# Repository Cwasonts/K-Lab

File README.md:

# K-Lab
storing boards I make for lab

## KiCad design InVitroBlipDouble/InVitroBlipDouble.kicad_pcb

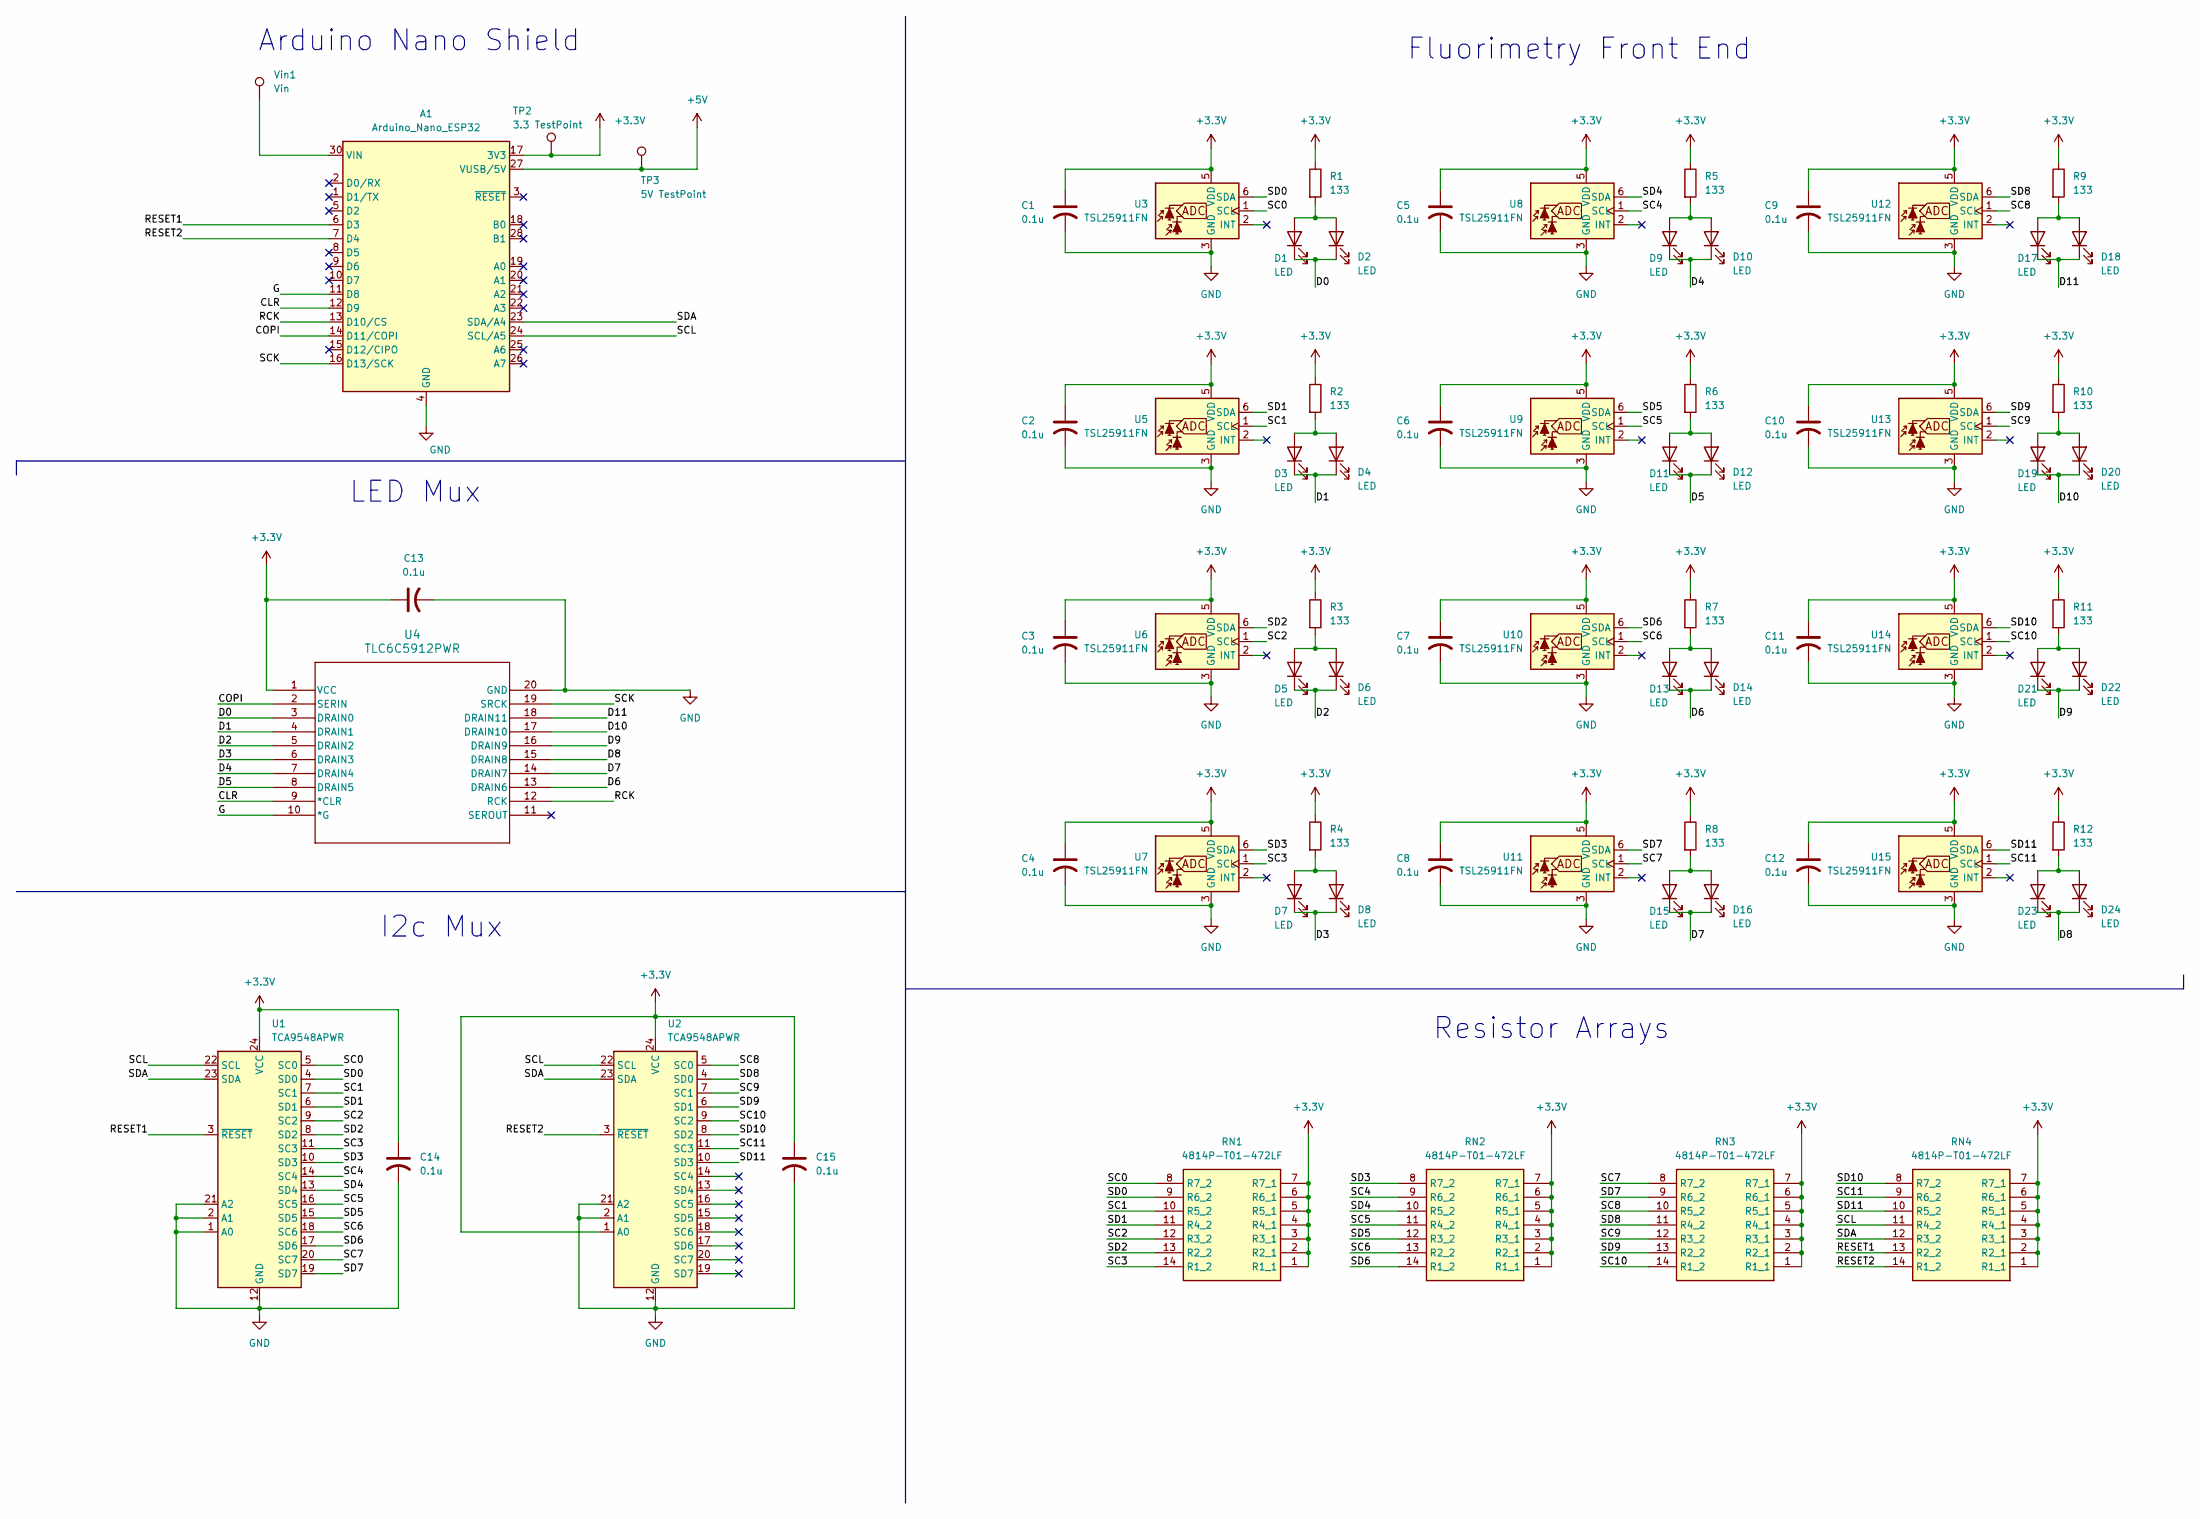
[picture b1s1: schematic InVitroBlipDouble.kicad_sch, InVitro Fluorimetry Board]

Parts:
A1: Arduino_Nano_ESP32; Arduino_Nano
C1, C2, C3, C4, C5, C6, C7, C8, C9, C10, C11, C12, C13, C14, C15: 0.1u; C_0603_1608Metric
D1, D2, D3, D4, D5, D6, D7, D8, D9, D10, D11, D12, D13, D14, D15, D16, D17, D18, D19, D20, D21, D22, D23, D24: LED; LED_Cree-XQ
R1, R2, R3, R4, R5, R6, R7, R8, R9, R10, R11, R12: 133; R_0603_1608Metric
RN1, RN2, RN3, RN4: 4814P-T01-472LF; 4814PT01472LF; Mouser Part Number 652-4814P-T1LF-4.7K
TP2: 3.3 TestPoint; TestPoint_Pad_2.5x2.5mm
TP3: 5V TestPoint; TestPoint_Pad_2.5x2.5mm
U1, U2: TCA9548APWR; TSSOP-24_4.4x7.8mm_P0.65mm
U3, U5, U6, U7, U8, U9, U10, U11, U12, U13, U14, U15: TSL25911FN; AMS_TSL25911FN
U4: TLC6C5912PWR; PW20_TEX
Vin1: Vin; TestPoint_Pad_2.5x2.5mm

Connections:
+3.3V: A1.17 (3V3), C1.1, C2.1, C3.1, C4.1, C5.1, C6.1, C7.1, C8.1, C9.1, C10.1, C11.1, C12.1, C13.1, C14.1, C15.1, R1.1, R2.1, R3.1, R4.1, R5.1, R6.1, R7.1, R8.1, R9.1, R10.1, R11.1, R12.1, RN1.1 (R1_1), RN1.2 (R2_1), RN1.3 (R3_1), RN1.4 (R4_1), RN1.5 (R5_1), RN1.6 (R6_1), RN1.7 (R7_1), RN2.1 (R1_1), RN2.2 (R2_1), RN2.3 (R3_1), RN2.4 (R4_1), RN2.5 (R5_1), RN2.6 (R6_1), RN2.7 (R7_1), RN3.1 (R1_1), RN3.2 (R2_1), RN3.3 (R3_1), RN3.4 (R4_1), RN3.5 (R5_1), RN3.6 (R6_1), RN3.7 (R7_1), RN4.1 (R1_1), RN4.2 (R2_1), RN4.3 (R3_1), RN4.4 (R4_1), RN4.5 (R5_1), RN4.6 (R6_1), RN4.7 (R7_1), TP2.1, U1.24 (VCC), U2.1 (A0), U2.24 (VCC), U3.5 (VDD), U4.1 (VCC), U5.5 (VDD), U6.5 (VDD), U7.5 (VDD), U8.5 (VDD), U9.5 (VDD), U10.5 (VDD), U11.5 (VDD), U12.5 (VDD), U13.5 (VDD), U14.5 (VDD), U15.5 (VDD); also elsewhere on the board
+5V: A1.27 (VUSB/5V), TP3.1; also elsewhere on the board
/CLR: A1.12 (D9), U4.9 (*CLR)
/COPI: A1.14 (D11/COPI), U4.2 (SERIN)
/D0: D1.1 (K), D2.1 (K), U4.3 (DRAIN0)
/D1: D3.1 (K), D4.1 (K), U4.4 (DRAIN1)
/D2: D5.1 (K), D6.1 (K), U4.5 (DRAIN2)
/D3: D7.1 (K), D8.1 (K), U4.6 (DRAIN3)
/D4: D9.1 (K), D10.1 (K), U4.7 (DRAIN4)
/D5: D11.1 (K), D12.1 (K), U4.8 (DRAIN5)
/D6: D13.1 (K), D14.1 (K), U4.13 (DRAIN6)
/D7: D15.1 (K), D16.1 (K), U4.14 (DRAIN7)
/D8: D23.1 (K), D24.1 (K), U4.15 (DRAIN8)
/D9: D21.1 (K), D22.1 (K), U4.16 (DRAIN9)
/D10: D19.1 (K), D20.1 (K), U4.17 (DRAIN10)
/D11: D17.1 (K), D18.1 (K), U4.18 (DRAIN11)
/G: A1.11 (D8), U4.10 (*G)
/RCK: A1.13 (D10/CS), U4.12 (RCK)
/RESET1: A1.6 (D3), RN4.13 (R2_2), U1.3 (~RESET)
/RESET2: A1.7 (D4), RN4.14 (R1_2), U2.3 (~RESET)
/SC0: RN1.8 (R7_2), U1.5 (SC0), U3.1 (SCL)
/SC1: RN1.10 (R5_2), U1.7 (SC1), U5.1 (SCL)
/SC2: RN1.12 (R3_2), U1.9 (SC2), U6.1 (SCL)
/SC3: RN1.14 (R1_2), U1.11 (SC3), U7.1 (SCL)
/SC4: RN2.9 (R6_2), U1.14 (SC4), U8.1 (SCL)
/SC5: RN2.11 (R4_2), U1.16 (SC5), U9.1 (SCL)
/SC6: RN2.13 (R2_2), U1.18 (SC6), U10.1 (SCL)
/SC7: RN3.8 (R7_2), U1.20 (SC7), U11.1 (SCL)
/SC8: RN3.10 (R5_2), U2.5 (SC0), U12.1 (SCL)
/SC9: RN3.12 (R3_2), U2.7 (SC1), U13.1 (SCL)
/SC10: RN3.14 (R1_2), U2.9 (SC2), U14.1 (SCL)
/SC11: RN4.9 (R6_2), U2.11 (SC3), U15.1 (SCL)
/SCK: A1.16 (D13/SCK), U4.19 (SRCK)
/SCL: A1.24 (SCL/A5), RN4.11 (R4_2), U1.22 (SCL), U2.22 (SCL)
/SD0: RN1.9 (R6_2), U1.4 (SD0), U3.6 (SDA)
/SD1: RN1.11 (R4_2), U1.6 (SD1), U5.6 (SDA)
/SD2: RN1.13 (R2_2), U1.8 (SD2), U6.6 (SDA)
/SD3: RN2.8 (R7_2), U1.10 (SD3), U7.6 (SDA)
/SD4: RN2.10 (R5_2), U1.13 (SD4), U8.6 (SDA)
/SD5: RN2.12 (R3_2), U1.15 (SD5), U9.6 (SDA)
/SD6: RN2.14 (R1_2), U1.17 (SD6), U10.6 (SDA)
/SD7: RN3.9 (R6_2), U1.19 (SD7), U11.6 (SDA)
/SD8: RN3.11 (R4_2), U2.4 (SD0), U12.6 (SDA)
/SD9: RN3.13 (R2_2), U2.6 (SD1), U13.6 (SDA)
/SD10: RN4.8 (R7_2), U2.8 (SD2), U14.6 (SDA)
/SD11: RN4.10 (R5_2), U2.10 (SD3), U15.6 (SDA)
/SDA: A1.23 (SDA/A4), RN4.12 (R3_2), U1.23 (SDA), U2.23 (SDA)
GND: A1.4 (GND), A1.29 (GND), C1.2, C2.2, C3.2, C4.2, C5.2, C6.2, C7.2, C8.2, C9.2, C10.2, C11.2, C12.2, C13.2, C14.2, C15.2, U1.1 (A0), U1.2 (A1), U1.12 (GND), U1.21 (A2), U2.2 (A1), U2.12 (GND), U2.21 (A2), U3.3 (GND), U4.20 (GND), U5.3 (GND), U6.3 (GND), U7.3 (GND), U8.3 (GND), U9.3 (GND), U10.3 (GND), U11.3 (GND), U12.3 (GND), U13.3 (GND), U14.3 (GND), U15.3 (GND)
unnamed 48: A1.30 (VIN), Vin1.1; also elsewhere on the board
unnamed: D1.2 (A), D2.2 (A), R1.2
unnamed: D3.2 (A), D4.2 (A), R2.2
unnamed: D5.2 (A), D6.2 (A), R3.2
unnamed: D7.2 (A), D8.2 (A), R4.2
unnamed: D9.2 (A), D10.2 (A), R5.2
unnamed: D11.2 (A), D12.2 (A), R6.2
unnamed: D13.2 (A), D14.2 (A), R7.2
unnamed: D15.2 (A), D16.2 (A), R8.2
unnamed: D17.2 (A), D18.2 (A), R9.2
unnamed: D19.2 (A), D20.2 (A), R10.2
unnamed: D21.2 (A), D22.2 (A), R11.2
unnamed: D23.2 (A), D24.2 (A), R12.2

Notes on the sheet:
Resistor Arrays
LED Mux
Fluorimetry Front End
I2c Mux
Arduino Nano Shield

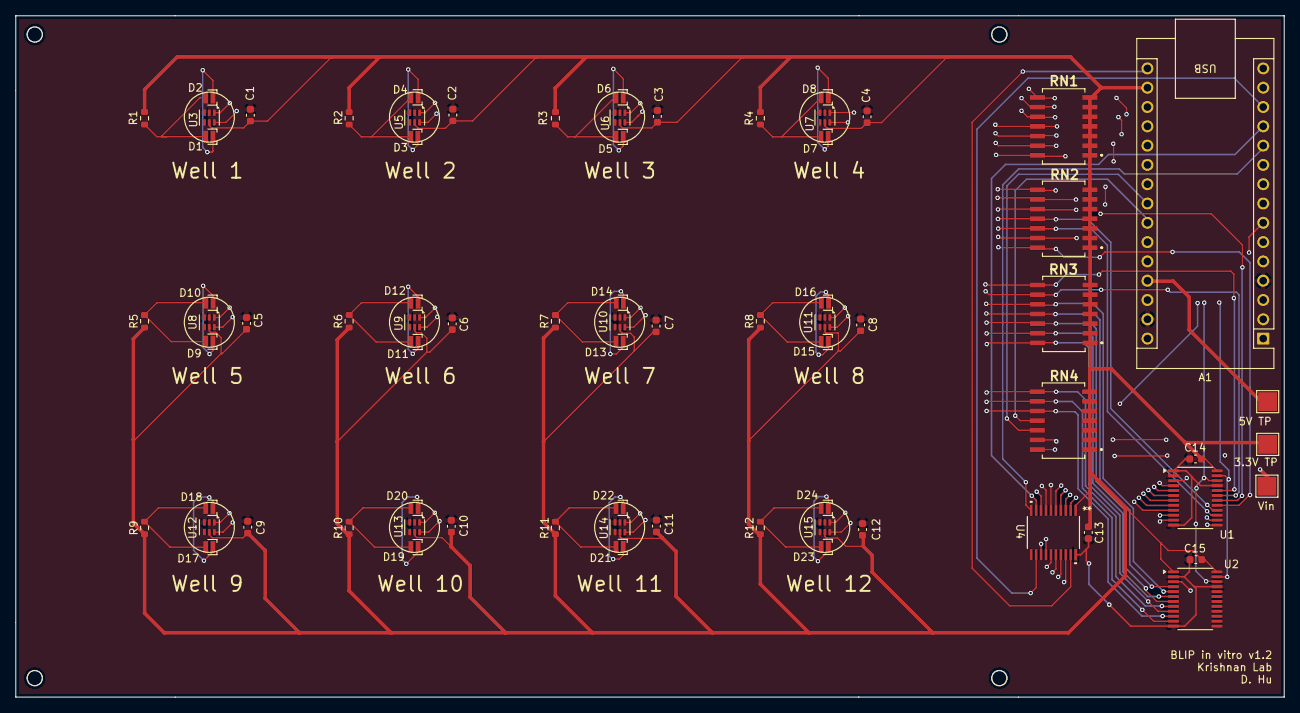
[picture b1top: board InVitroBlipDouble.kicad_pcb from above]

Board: 4 copper layers, 167.0 x 89.7 mm, 74 parts (0 on the bottom side), 61 nets.

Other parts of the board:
3.3V TP: 3.3 TestPoint; TestPoint_Pad_2.5x2.5mm
5V TP: 5V TestPoint; TestPoint_Pad_2.5x2.5mm
Vin: Vin; TestPoint_Pad_2.5x2.5mm

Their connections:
+3.3V: 3.3V TP.1 (1_1); also elsewhere on the board
+5V: 5V TP.1 (1_1); also elsewhere on the board
unnamed 48: Vin.1 (1_1); also elsewhere on the board

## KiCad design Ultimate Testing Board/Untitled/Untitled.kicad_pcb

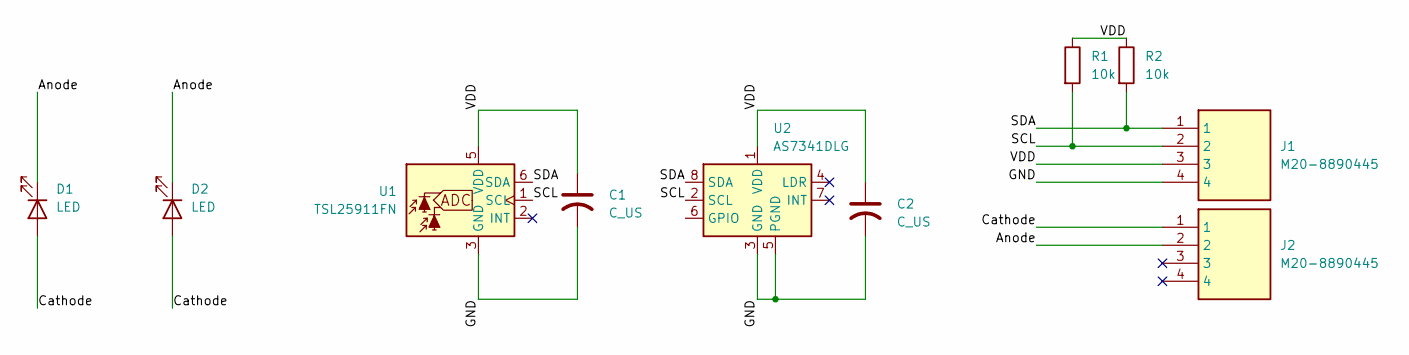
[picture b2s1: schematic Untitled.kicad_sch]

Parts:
C1, C2: C_US; C_0402_1005Metric
D1: LED; LED_Cree-XP
D2: LED; LED_Cree-XQ
J1, J2: M20-8890445; M208890445; Mouser Part Number 855-M20-8890445
R1, R2: 10k; R_0402_1005Metric
U1: TSL25911FN; AMS_TSL25911FN
U2: AS7341DLG; AMS_OLGA-8_2x3.1mm_P0.8mm

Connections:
/Anode: D1.1 (K), D2.1 (K), J2.2
/Cathode: D1.2 (A), D2.2 (A), J2.1
/GND: C1.2, C2.2, J1.4, U1.3 (GND), U2.3 (GND), U2.5 (PGND)
/SCL: J1.2, R1.2, U1.1 (SCL), U2.2 (SCL)
/SDA: J1.1, R2.2, U1.6 (SDA), U2.8 (SDA)
/VDD: C1.1, C2.1, J1.3, R1.1, R2.1, U1.5 (VDD), U2.1 (VDD)

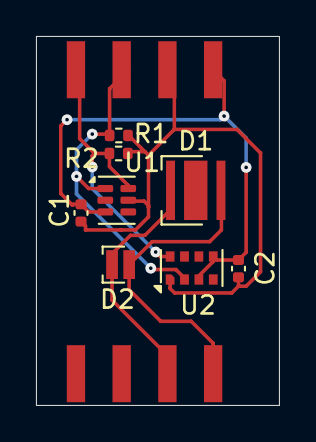
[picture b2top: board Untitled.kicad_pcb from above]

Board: 2 copper layers, 13.5 x 20.5 mm, 10 parts (0 on the bottom side), 6 nets.

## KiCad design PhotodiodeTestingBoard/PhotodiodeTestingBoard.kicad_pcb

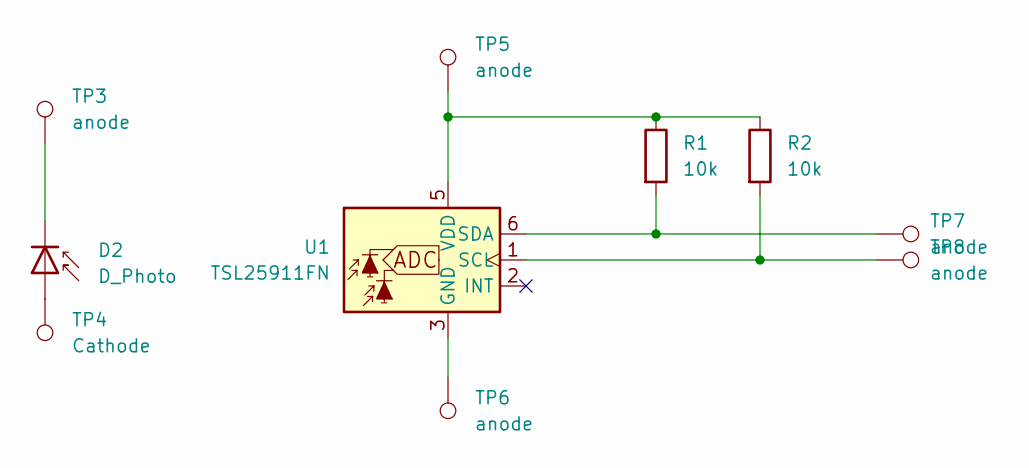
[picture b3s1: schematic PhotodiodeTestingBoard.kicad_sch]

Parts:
D2: D_Photo; LED_Cree-XP
R1, R2: 10k; R_0603_1608Metric
TP3, TP5, TP6, TP7, TP8: anode; TestPoint_Pad_2.0x2.0mm
TP4: Cathode; TestPoint_Pad_2.0x2.0mm
U1: TSL25911FN; AMS_TSL25911FN

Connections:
unnamed: D2.2 (A), TP4.1 (1_1)
unnamed: D2.1 (K), TP3.1 (1_1)
unnamed: TP6.1 (1_1), U1.3 (GND)
unnamed: R2.2, TP8.1 (1_1), U1.1 (SCL)
unnamed: R1.2, TP7.1 (1_1), U1.6 (SDA)
unnamed: R1.1, R2.1, TP5.1 (1_1), U1.5 (VDD)

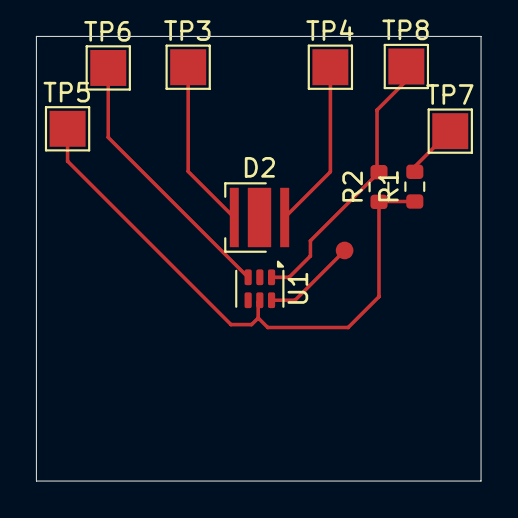
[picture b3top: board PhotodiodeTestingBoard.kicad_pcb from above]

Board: 2 copper layers, 24.7 x 24.7 mm, 10 parts (0 on the bottom side), 6 nets.

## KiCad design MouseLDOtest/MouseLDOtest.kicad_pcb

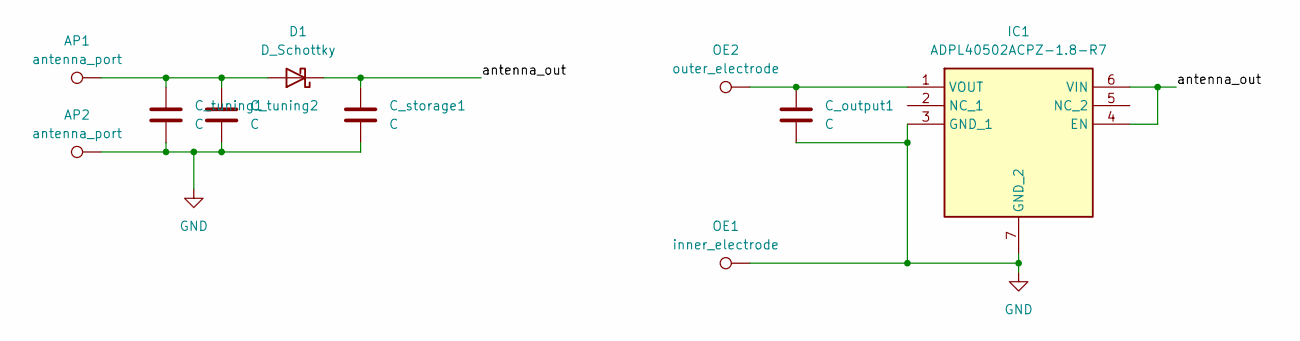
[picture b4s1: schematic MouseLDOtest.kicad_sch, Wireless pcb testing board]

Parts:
AP1, AP2: antenna_port; TestPoint_Pad_D2.0mm
C_output1: C; C_0402_1005Metric
C_storage1: C; C_0402_1005Metric
C_tuning1, C_tuning2: C; C_0402_1005Metric
D1: D_Schottky; D_0402_1005Metric
IC1: ADPL40502ACPZ-1.8-R7; CP-6-3_ADI; Manufacturer_Part_Number ADPL40502ACPZ-1.8-R7
OE1: inner_electrode; TestPoint_Pad_D2.0mm
OE2: outer_electrode; TestPoint_Pad_D2.0mm

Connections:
/antenna_out: C_storage1.1, D1.1 (K), IC1.4 (EN), IC1.6 (VIN)
GND: AP2.1 (1_1), C_output1.2, C_storage1.2, C_tuning1.2, C_tuning2.2, IC1.3 (GND_1), IC1.7 (GND_2), OE1.1 (1_1)
unnamed: AP1.1 (1_1), C_tuning1.1, C_tuning2.1, D1.2 (A)
unnamed: C_output1.1, IC1.1 (VOUT), OE2.1 (1_1)

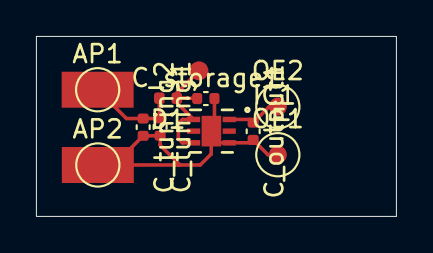
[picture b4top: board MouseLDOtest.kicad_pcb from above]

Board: 2 copper layers, 20.0 x 10.0 mm, 10 parts (0 on the bottom side), 4 nets.

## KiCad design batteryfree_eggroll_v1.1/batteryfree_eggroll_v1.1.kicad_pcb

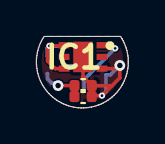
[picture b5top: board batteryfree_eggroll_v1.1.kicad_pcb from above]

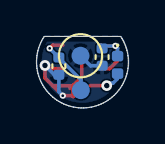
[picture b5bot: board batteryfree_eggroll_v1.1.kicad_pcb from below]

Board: 2 copper layers, 5.1 x 4.0 mm, 7 parts (4 on the bottom side), 4 nets.

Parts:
C_output1: C; C_0402_1005Metric
C_storage1: C; C_0402_1005Metric
C_tuning1, C_tuning2: C; C_0402_1005Metric
D1: D_Schottky; D_0402_1005Metric
IC1: ADPL40502ACPZ-1.8-R7; SON65P200X200X60-7N-D
OE1: inner_electrode; TestPoint_Pad_D2.0mm

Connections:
/antenna_out: C_storage1.1, D1.1 (K), IC1.4 (EN), IC1.6 (VIN)
GND: C_output1.2, C_storage1.2, C_tuning1.2, C_tuning2.2, IC1.3 (GND_1), IC1.7 (GND_2), OE1.1 (1_1)
unnamed: C_tuning1.1, C_tuning2.1, D1.2 (A)
unnamed: C_output1.1, IC1.1 (VOUT)

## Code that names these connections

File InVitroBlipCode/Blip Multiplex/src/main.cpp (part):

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#include <SPI.h>

// ---------------- Pin map (from the Nano shield schematic) ----------------
const int PIN_MUX1_RESET = D3;   // RESET1 -> U1 /RESET (active low)
const int PIN_MUX2_RESET = D4;   // RESET2 -> U2 /RESET (active low)
const int PIN_LED_G      = D8;   // TLC6C5912 /G   output enable (active low)
const int PIN_LED_CLR    = D9;   // TLC6C5912 /CLR clear (active low)
const int PIN_LED_RCK    = D10;  // TLC6C5912 RCK  latch
// SER IN = D11 (COPI), SRCK = D13 (SCK) -> driven by hardware SPI
// SDA = A4, SCL = A5 -> Wire defaults

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  digitalWrite(PIN_LED_CLR, LOW);    // clear all registers
  delayMicroseconds(1);
  digitalWrite(PIN_LED_CLR, HIGH);
  SPI.begin();                       // SCK=D13, CIPO=D12, COPI=D11
  ledWrite(0);
  digitalWrite(PIN_LED_G, LOW);      // enable outputs
}
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
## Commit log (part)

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2026-06-25 Add project title and description to README
2026-06-25 Initial Boards
